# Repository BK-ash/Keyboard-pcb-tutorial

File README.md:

# Keyboard pcb tutorial
 My attempt at making custom PCB for the womier k66, so that i can have one that actually has good QMK support so i can edit all the rgb including the underglow

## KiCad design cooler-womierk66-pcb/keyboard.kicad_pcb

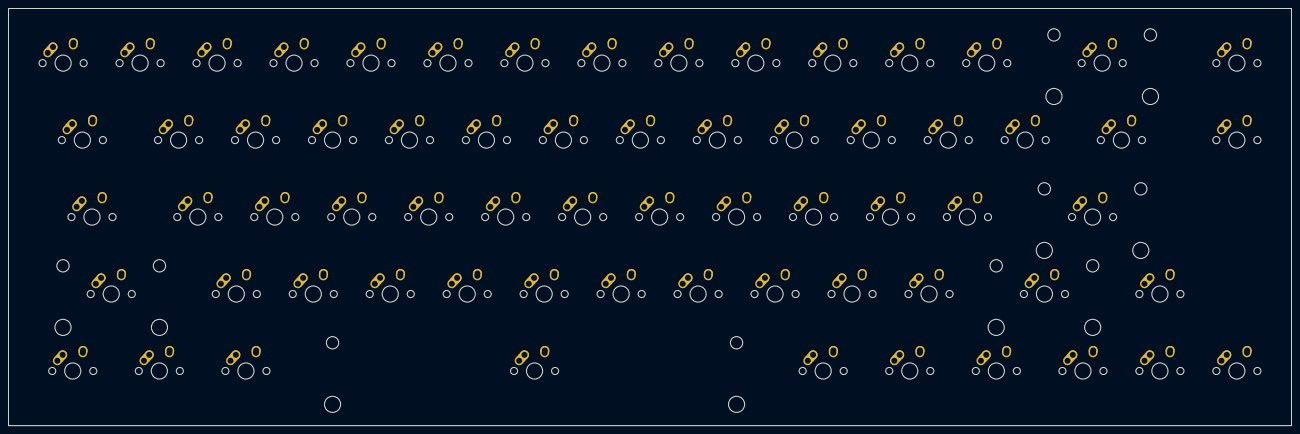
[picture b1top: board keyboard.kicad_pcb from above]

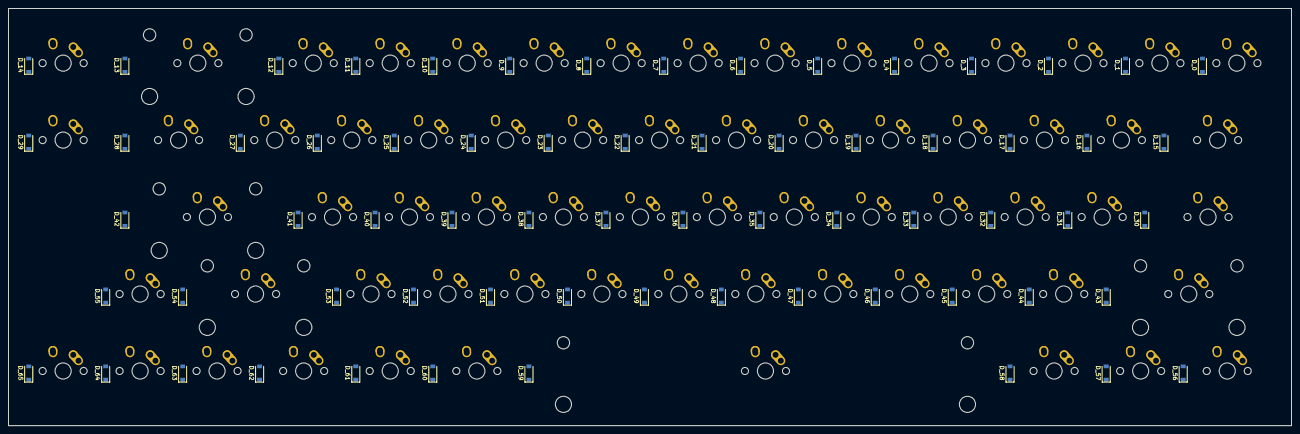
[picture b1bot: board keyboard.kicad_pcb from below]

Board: 2 copper layers, 317.6 x 103.2 mm, 132 parts (66 on the bottom side), 87 nets, no tracks yet.

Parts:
D_0, D_1, D_2, D_3, D_4, D_5, D_6, D_7, D_8, D_9, D_10, D_11, D_12, D_13, D_14, D_15, D_16, D_17, D_18, D_19, D_20, D_21, D_22, D_23, D_24, D_25, D_26, D_27, D_28, D_29, D_30, D_31, D_32, D_33, D_34, D_35, D_36, D_37, D_38, D_39, D_40, D_41, D_42, D_43, D_44, D_45, D_46, D_47, D_48, D_49, D_50, D_51, D_52, D_53, D_54, D_55, D_56, D_57, D_58, D_59, D_60, D_61, D_62, D_63, D_64, D_65: D; D_SOD-123
K_0, K_1, K_2, K_3, K_4, K_5, K_6, K_7, K_8, K_9, K_10, K_11, K_12, K_14, K_16, K_17, K_18, K_19, K_20, K_21, K_22, K_23, K_24, K_25, K_26, K_27, K_29, K_31, K_32, K_33, K_34, K_35, K_36, K_37, K_38, K_39, K_40, K_41, K_44, K_45, K_46, K_47, K_48, K_49, K_50, K_51, K_52, K_53, K_55, K_57, K_61, K_63, K_64, K_65: KEYSW; MX-1U-NoLED
K_13, K_54: KEYSW; MX-2U-NoLED
K_15, K_28: KEYSW; MX-1.5U-NoLED
K_30: KEYSW; MX-1.75U-NoLED
K_42, K_43: KEYSW; MX-2.25U-NoLED
K_56, K_58, K_60, K_62: KEYSW; MX-1.25U-NoLED
K_59: KEYSW; MX-6.25U-NoLED

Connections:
unnamed: D_0.2, K_0.2
unnamed: D_1.2, K_1.2
unnamed: D_2.2, K_2.2
unnamed: D_3.2, K_3.2
unnamed: D_4.2, K_4.2
unnamed: D_5.2, K_5.2
unnamed: D_6.2, K_6.2
unnamed: D_7.2, K_7.2
unnamed: D_8.2, K_8.2
unnamed: D_9.2, K_9.2
unnamed: D_10.2, K_10.2
unnamed: D_11.2, K_11.2
unnamed: D_12.2, K_12.2
unnamed: D_13.2, K_13.2
unnamed: D_14.2, K_14.2
unnamed: D_15.2, K_15.2
unnamed: D_16.2, K_16.2
unnamed: D_17.2, K_17.2
unnamed: D_18.2, K_18.2
unnamed: D_19.2, K_19.2
unnamed: D_20.2, K_20.2
unnamed: D_21.2, K_21.2
unnamed: D_22.2, K_22.2
unnamed: D_23.2, K_23.2
unnamed: D_24.2, K_24.2
unnamed: D_25.2, K_25.2
unnamed: D_26.2, K_26.2
unnamed: D_27.2, K_27.2
unnamed: D_28.2, K_28.2
unnamed: D_29.2, K_29.2
unnamed: D_30.2, K_30.2
unnamed: D_31.2, K_31.2
unnamed: D_32.2, K_32.2
unnamed: D_33.2, K_33.2
unnamed: D_34.2, K_34.2
unnamed: D_35.2, K_35.2
unnamed: D_36.2, K_36.2
unnamed: D_37.2, K_37.2
unnamed: D_38.2, K_38.2
unnamed: D_39.2, K_39.2
unnamed: D_40.2, K_40.2
unnamed: D_41.2, K_41.2
unnamed: D_42.2, K_42.2
unnamed: D_43.2, K_43.2
unnamed: D_44.2, K_44.2
unnamed: D_45.2, K_45.2
unnamed: D_46.2, K_46.2
unnamed: D_47.2, K_47.2
unnamed: D_48.2, K_48.2
unnamed: D_49.2, K_49.2
unnamed: D_50.2, K_50.2
unnamed: D_51.2, K_51.2
unnamed: D_52.2, K_52.2
unnamed: D_53.2, K_53.2
unnamed: D_54.2, K_54.2
unnamed: D_55.2, K_55.2
unnamed: D_56.2, K_56.2
unnamed: D_57.2, K_57.2
unnamed: D_58.2, K_58.2
unnamed: D_59.2, K_59.2
unnamed: D_60.2, K_60.2
unnamed: D_61.2, K_61.2
unnamed: D_62.2, K_62.2
unnamed: D_63.2, K_63.2
unnamed: D_64.2, K_64.2
unnamed: D_65.2, K_65.2
col0: K_0.1, K_15.1, K_30.1, K_56.1
col1: K_1.1, K_43.1, K_57.1
col2: K_2.1, K_16.1, K_31.1, K_44.1, K_58.1
col3: K_3.1, K_17.1, K_32.1, K_45.1
col4: K_4.1, K_18.1, K_33.1, K_46.1
col5: K_5.1, K_19.1, K_34.1, K_47.1
col6: K_6.1, K_20.1, K_35.1, K_48.1, K_59.1
col7: K_7.1, K_21.1, K_36.1, K_49.1
col8: K_8.1, K_22.1, K_37.1, K_50.1
col9: K_9.1, K_23.1, K_38.1, K_51.1
col10: K_10.1, K_24.1, K_39.1, K_52.1, K_60.1
col11: K_11.1, K_25.1, K_40.1, K_53.1, K_61.1
col12: K_12.1, K_26.1, K_41.1, K_62.1
col13: K_27.1, K_42.1, K_54.1, K_63.1
col14: K_13.1, K_28.1, K_55.1, K_64.1
col15: K_14.1, K_29.1, K_65.1
row0: D_0.1, D_1.1, D_2.1, D_3.1, D_4.1, D_5.1, D_6.1, D_7.1, D_8.1, D_9.1, D_10.1, D_11.1, D_12.1, D_13.1, D_14.1
row1: D_15.1, D_16.1, D_17.1, D_18.1, D_19.1, D_20.1, D_21.1, D_22.1, D_23.1, D_24.1, D_25.1, D_26.1, D_27.1, D_28.1, D_29.1
row2: D_30.1, D_31.1, D_32.1, D_33.1, D_34.1, D_35.1, D_36.1, D_37.1, D_38.1, D_39.1, D_40.1, D_41.1, D_42.1
row3: D_43.1, D_44.1, D_45.1, D_46.1, D_47.1, D_48.1, D_49.1, D_50.1, D_51.1, D_52.1, D_53.1, D_54.1, D_55.1
row4: D_56.1, D_57.1, D_58.1, D_59.1, D_60.1, D_61.1, D_62.1, D_63.1, D_64.1, D_65.1

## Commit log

2021-07-23 part2step3
2021-07-24 Add submodules
2021-07-24 part2step4
2021-07-25 part4 step 6
2021-07-26 Part 4 done, part 5 now.
2021-07-26 Before the step where I start routing
